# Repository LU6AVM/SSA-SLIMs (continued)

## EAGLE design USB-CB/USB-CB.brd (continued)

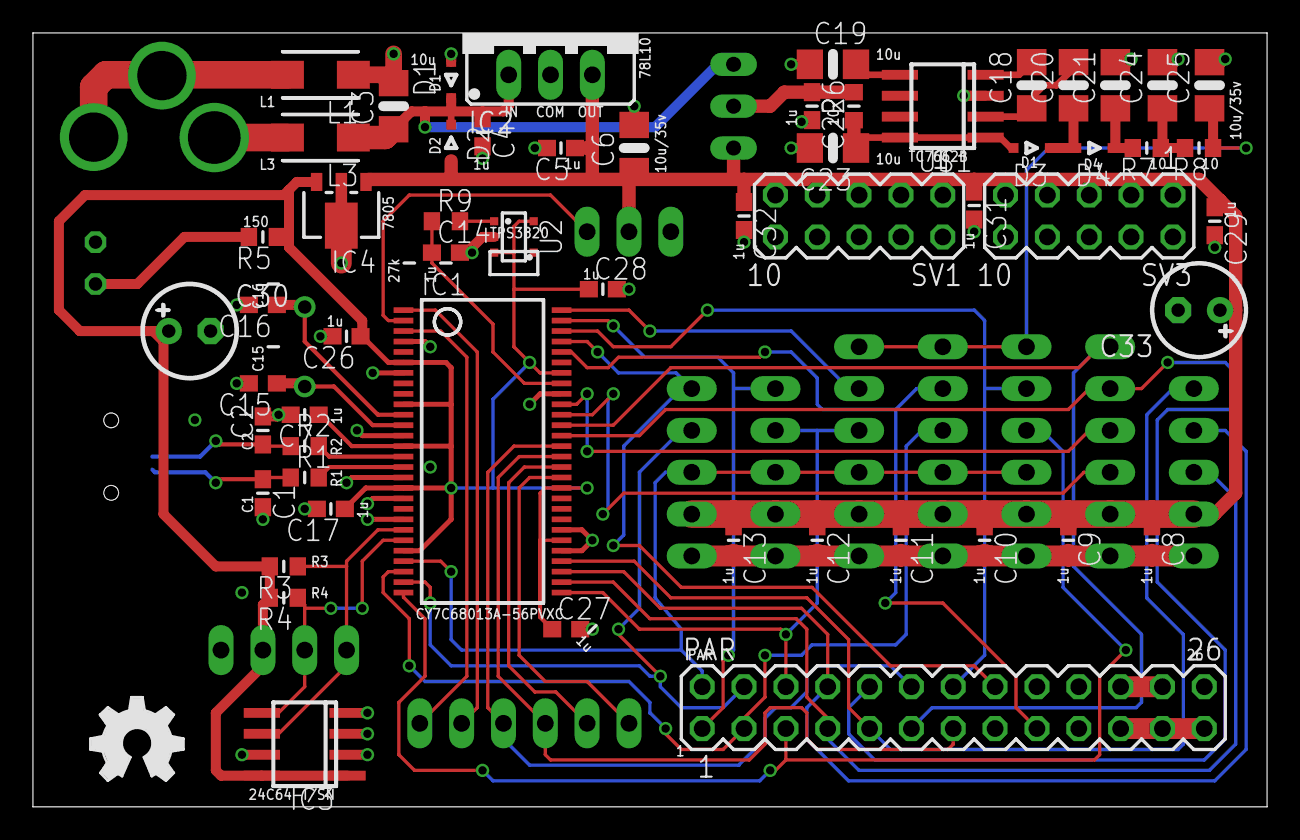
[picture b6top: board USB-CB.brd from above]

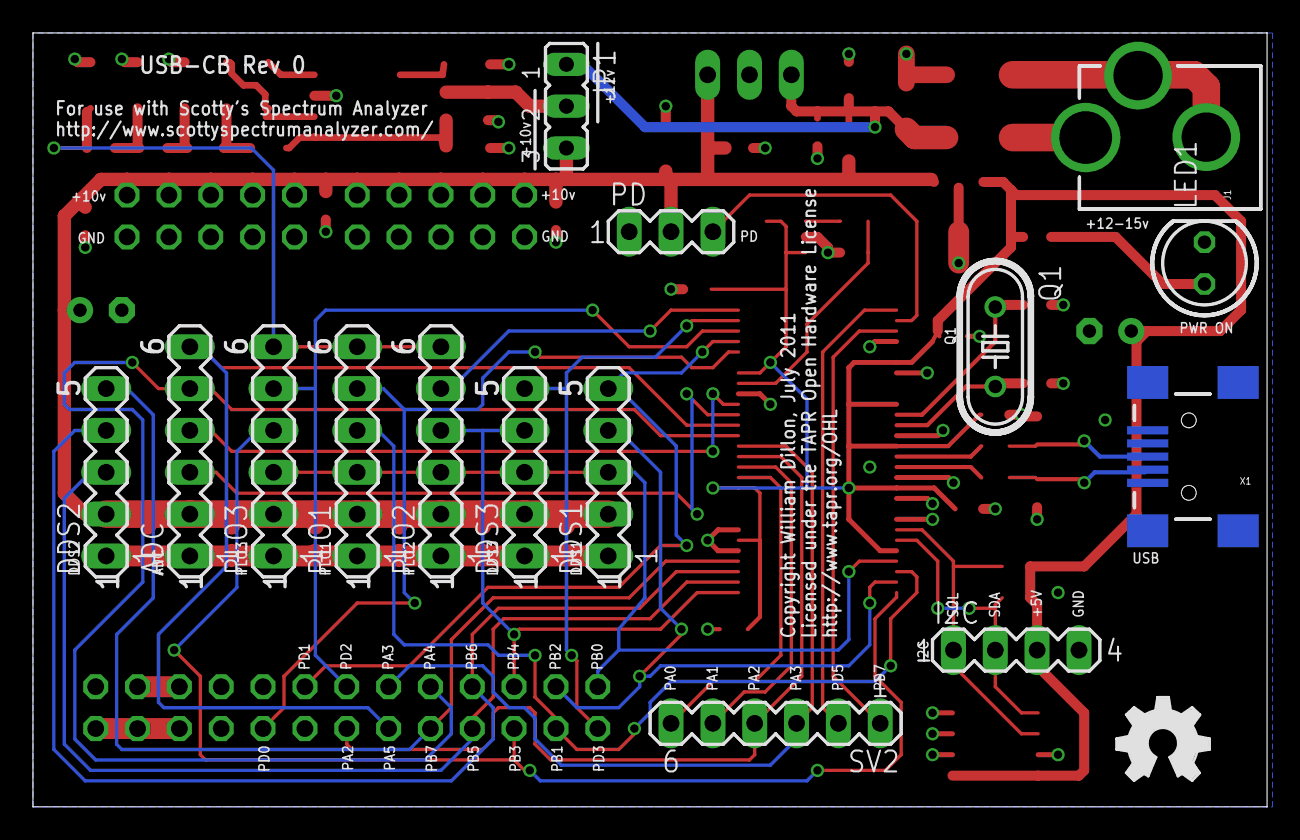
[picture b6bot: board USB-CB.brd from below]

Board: 2 copper layers, 74.9 x 47.0 mm, 73 parts (15 on the bottom side), 50 nets.

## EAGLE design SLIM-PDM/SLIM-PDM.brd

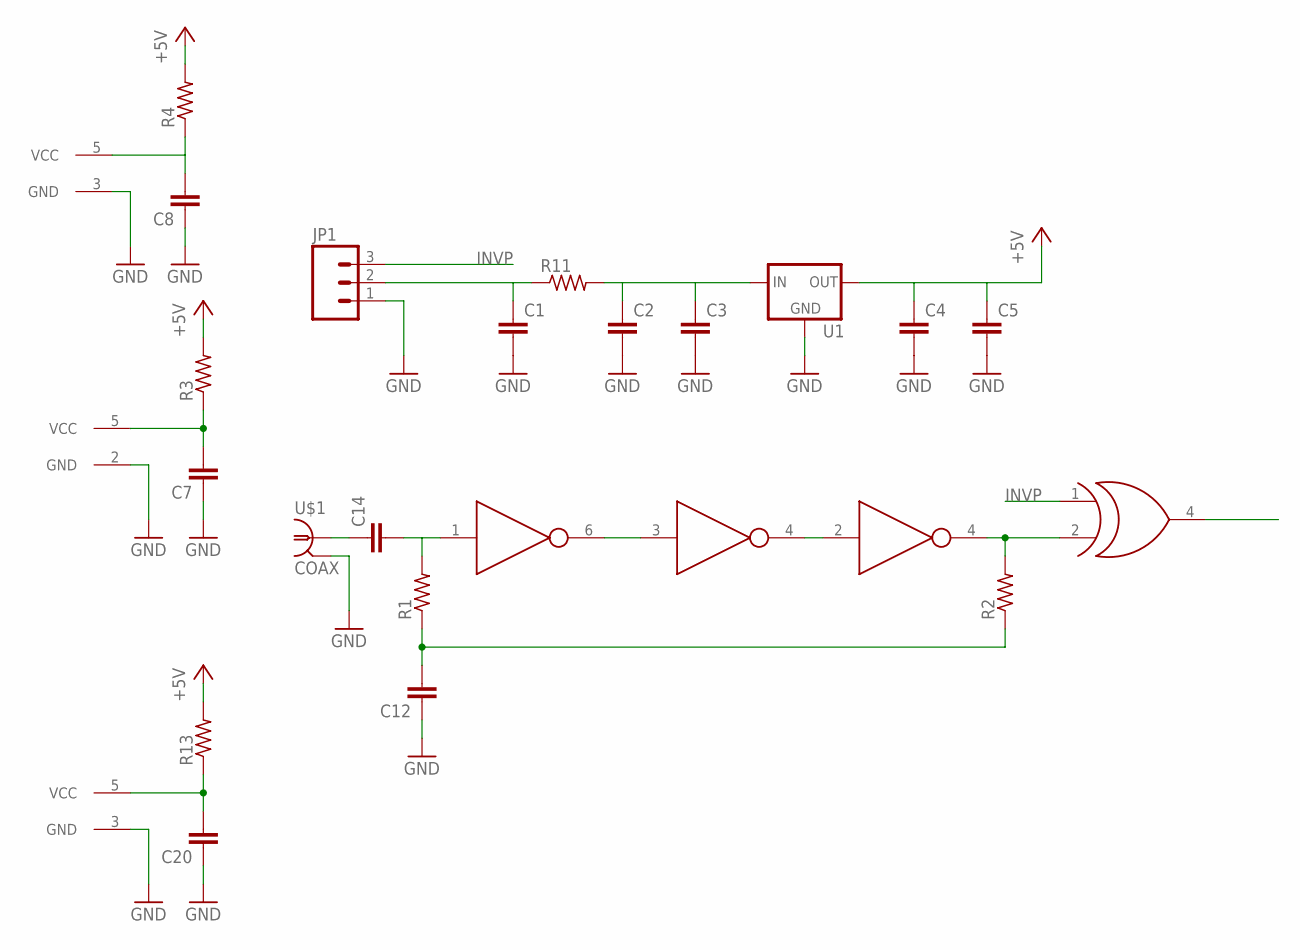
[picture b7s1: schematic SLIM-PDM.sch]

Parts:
C1, C2, C4, C7, C8, C12, C14, C20: C-EUC0805; C0805
C3: C-EUC1206; C1206
C5: C-EUC3216; C3216
JP1: M03PTH; 1X03
R1, R2, R3, R4, R11, R13: R-US_R0805; R0805
U1: 78MXXLSOT-89; SOT89-BCE
U2: 7WZU04; SC70-6L
U3: 7SZ04; SOT23-5L
U$1: COAX; SLIM_COAX_PAD
U$2: 74LVC1G86; SOT23-5L

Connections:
+5V: C4.1, C5.1, R3.2, R4.2, R13.2, U1.B (OUT)
GND: C1.2, C2.2, C3.2, C4.2, C5.2, C7.1, C8.1, C12.1, C20.1, JP1.1, U1.C (GND), U2.2 (GND), U3.3 (GND), U$1.P$2 (GND), U$2.3 (GND)
INVP: JP1.3, U$2.1 (A)
unnamed: C14.1, U$1.P$1 (1)
unnamed: C1.1, JP1.2, R11.1
unnamed: C2.1, C3.1, R11.2, U1.E (IN)
unnamed: C14.2, R1.2, U2.1 (IN)
unnamed: U2.3 (IN), U2.6 (OUT)
unnamed: U2.4 (OUT), U3.2 (IN)
unnamed: C7.2, R3.1, U2.5 (VCC)
unnamed: C12.2, R1.1, R2.1
unnamed: C20.2, R13.1, U3.5 (VCC)
unnamed: R2.2, U3.4 (OUT), U$2.2 (B)
unnamed: C8.2, R4.1, U$2.5 (VCC)

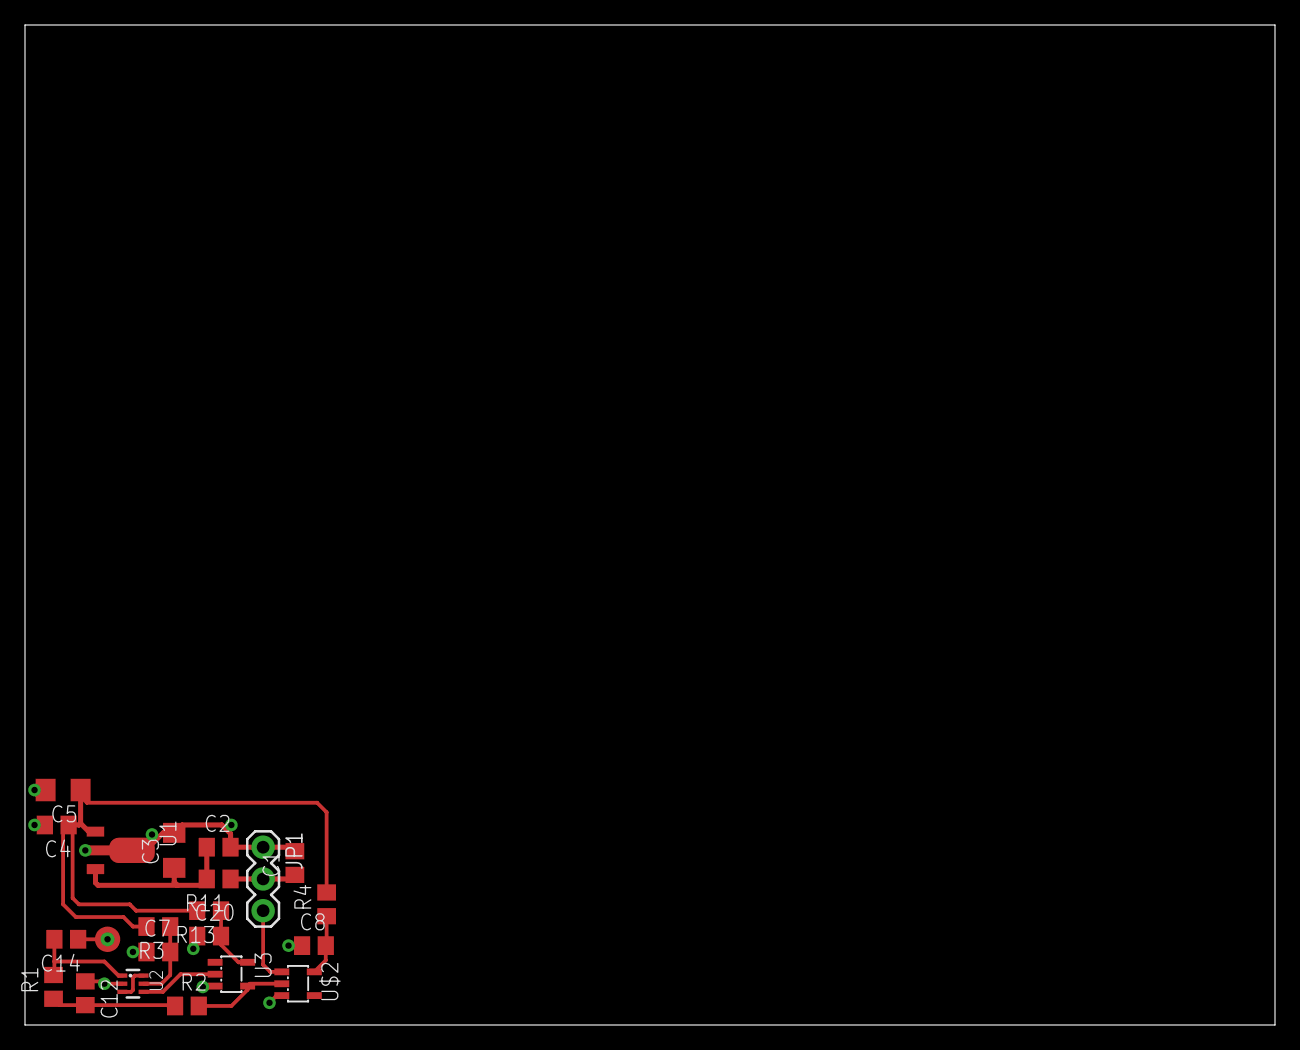
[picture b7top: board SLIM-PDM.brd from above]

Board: 2 copper layers, 100.0 x 80.0 mm, 22 parts (0 on the bottom side), 14 nets.

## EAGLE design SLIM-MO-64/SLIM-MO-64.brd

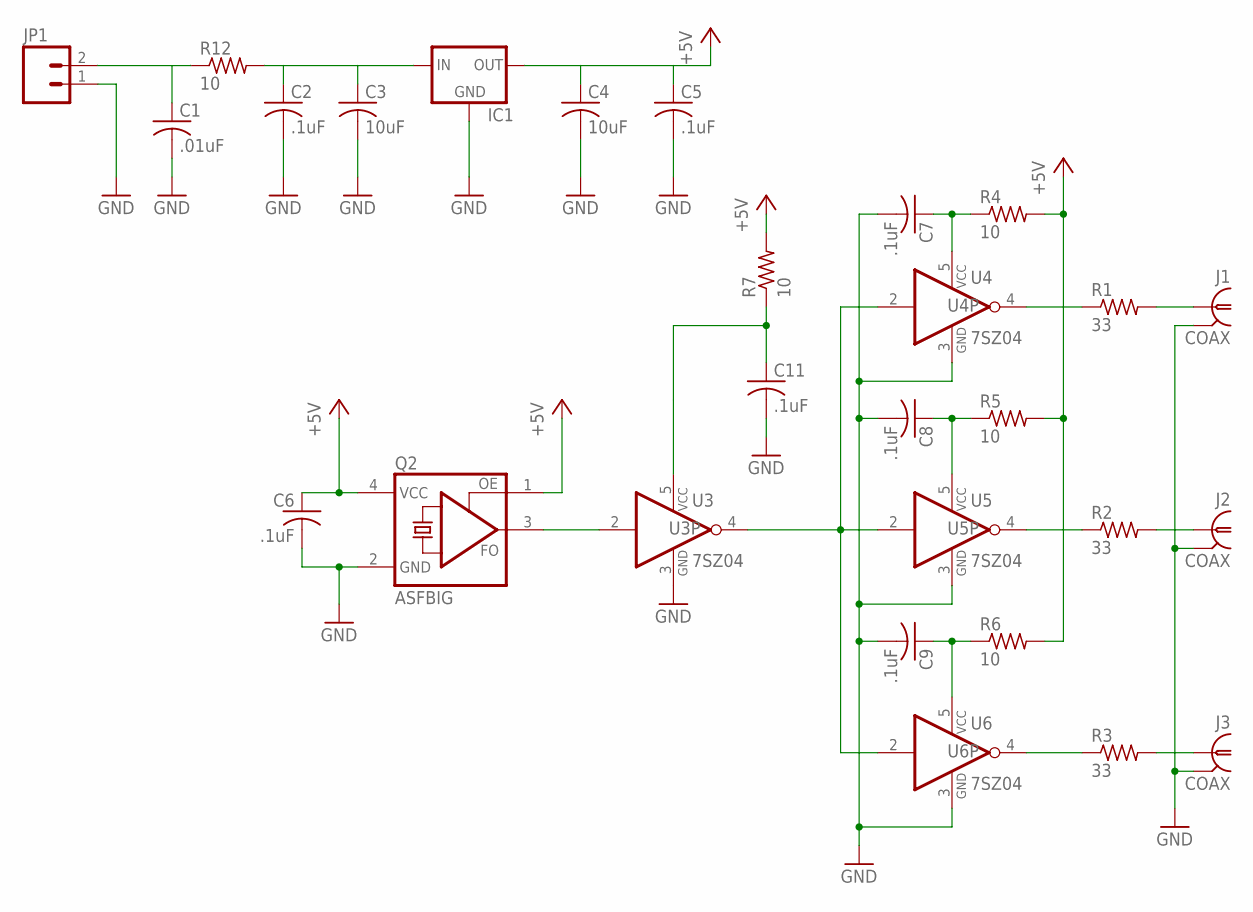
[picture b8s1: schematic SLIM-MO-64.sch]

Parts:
C1: .01uF; C0805
C2, C5, C6, C7, C8, C9, C11: .1uF; C0805
C3, C4: 10uF; C1206
IC1: 78MXXLDPAK; TO252
J1, J2, J3: COAX; SLIM_COAX_PAD
JP1: M02POLAR; MOLEX-1X2
Q2: ASFBIG; CTS507
R1, R2, R3: 33; R0805
R4, R5, R6, R7, R12: 10; R0805
U3, U4, U5, U6: 7SZ04; SOT23-5

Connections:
+5V: C4.1, C5.1, C6.1, IC1.2 (OUT), Q2.1 (OE), Q2.4 (VCC), R4.2, R5.2, R6.2, R7.2
GND: C1.2, C2.2, C3.2, C4.2, C5.2, C6.2, C7.2, C8.2, C9.2, C11.2, IC1.3 (GND), J1.P$2 (GND), J2.P$2 (GND), J3.P$2 (GND), JP1.1, Q2.2 (GND), U3.3 (GND), U4.3 (GND), U5.3 (GND), U6.3 (GND)
unnamed: C2.1, C3.1, IC1.1 (IN), R12.2
unnamed: C1.1, JP1.2, R12.1
unnamed: C11.1, R7.1, U3.5 (VCC)
unnamed: U3.4 (O), U4.2 (I), U5.2 (I), U6.2 (I)
unnamed: R1.1, U4.4 (O)
unnamed: R2.1, U5.4 (O)
unnamed: Q2.3 (FO), U3.2 (I)
unnamed: R3.1, U6.4 (O)
unnamed: C9.1, R6.1, U6.5 (VCC)
unnamed: C8.1, R5.1, U5.5 (VCC)
unnamed: C7.1, R4.1, U4.5 (VCC)
unnamed: J1.P$1 (1), R1.2
unnamed: J2.P$1 (1), R2.2
unnamed: J3.P$1 (1), R3.2

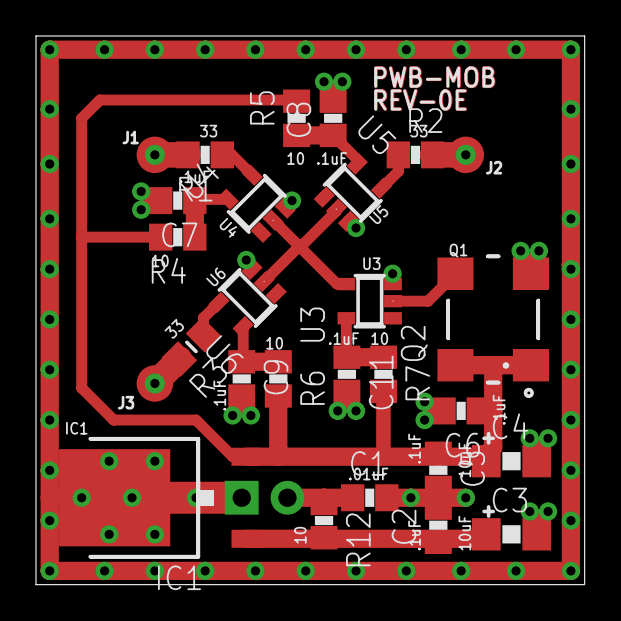
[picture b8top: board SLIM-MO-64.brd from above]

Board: 2 copper layers, 30.5 x 30.5 mm, 28 parts (1 on the bottom side), 16 nets.

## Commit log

2012-02-24 Initial import
    Initial Import of my Cadsoft Eagle ports of the SLIMs (Standard
    Laboratory Integration Modules) used in Scotty's Spectrum Analyzer.
2012-02-26 First commit of the ADC-16 board Added a CAM file to generate gerbers in gerber/
2012-02-27 Small changes to the control board shield, trying to improve current loop behavior
2012-03-10 Fixup the coax symbol to automatically connect the ground Add the DDS board Add a design rules file, based on the BatchPCB specs.
2012-03-21 Working on my ChipKit-based control board
    This is a work in progress.
2012-12-05 Final changes for SLIM-ADC-16 before sending off to fab.
